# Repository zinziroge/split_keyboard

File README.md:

# split_keyboard
split_keyboard.

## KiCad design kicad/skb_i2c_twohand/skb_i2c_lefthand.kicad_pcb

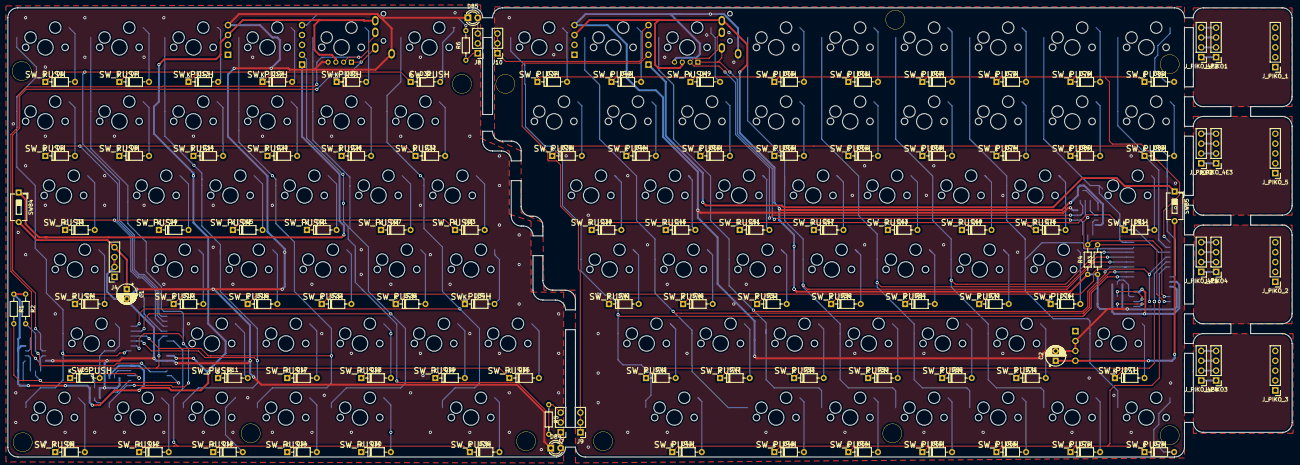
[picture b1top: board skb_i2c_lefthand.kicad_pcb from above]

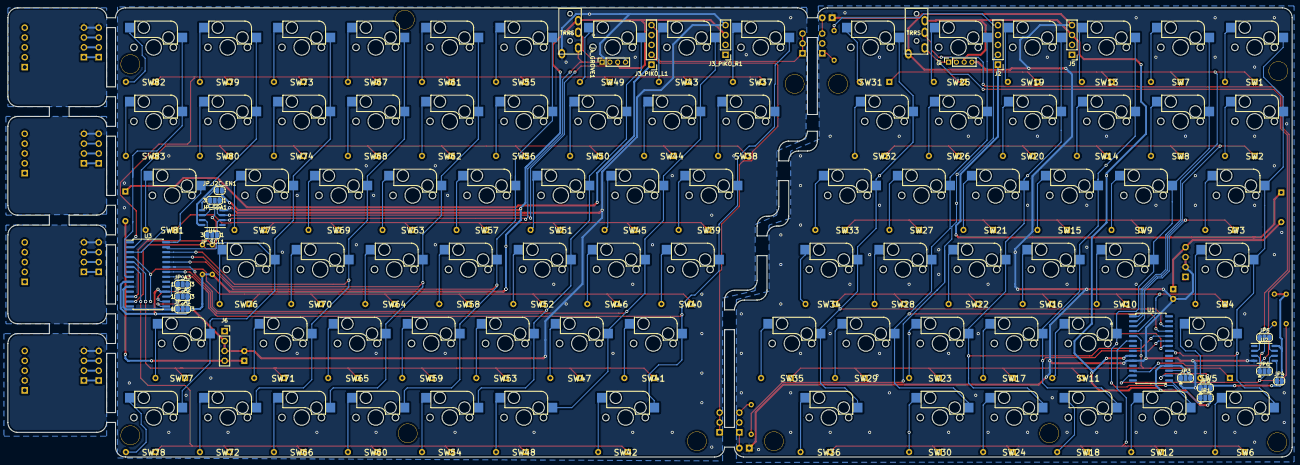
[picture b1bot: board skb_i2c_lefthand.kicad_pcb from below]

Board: 2 copper layers, 330.5 x 115.6 mm, 231 parts (108 on the bottom side), 162 nets.

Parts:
C1, C2: CP; CP_Radial_D5.0mm_P2.50mm
D1, D2, D3, D4, D5, D6, D7, D8, D9, D10, D11, D12, D13, D14, D15, D16, D17, D18, D19, D20, D21, D22, D23, D24, D25, D26, D27, D28, D29, D30, D31, D32, D33, D34, D35, D36, D37, D38, D39, D40, D41, D42, D43, D44, D45, D46, D47, D48, D49, D50, D51, D52, D53, D54, D55, D56, D57, D58, D59, D60, D61, D62, D63, D64, D65, D66, D67, D68, D69, D70, D71, D72, D73, D74, D75, D76, D77, D78, D79, D80, D81, D82, D83: 1N4148; D_DO-35_SOD27_P7.62mm_Horizontal
D84, D85: LED; LED_D3.0mm
J1, J2_TRRS1: MJ-4PP-9; MJ-4PP-9_1side
J2, J3_PIKO_L1: Conn_01x05_Male; PinHeader_1x05_P2.54mm_Vertical
J3, J4_GROVE1: Conn_01x04_Male; PinSocket_1x04_P2.00mm_Vertical
J3_PIKO_R1, J5: Conn_01x04_Male; PinHeader_1x04_P2.54mm_Vertical
J4: Power; PinSocket_1x04_P2.54mm_Vertical
J6: Conn_01x04; PinSocket_1x04_P2.54mm_Vertical
J7, J8, J9, J10: Conn_01x03; PinHeader_1x03_P2.54mm_Vertical
JP1: I2C_A0; SolderJumper-3_P1.3mm_Open_RoundedPad1.0x1.5mm
JP2: I2C_A1; SolderJumper-3_P1.3mm_Open_RoundedPad1.0x1.5mm
JP3: I2C_A2; SolderJumper-3_P1.3mm_Open_RoundedPad1.0x1.5mm
JP4: I2C_EN; SolderJumper-2_P1.3mm_Open_RoundedPad1.0x1.5mm
JP5: I2C_SCL; SolderJumper-3_P1.3mm_Open_RoundedPad1.0x1.5mm
JP6: I2C_SDA; SolderJumper-3_P1.3mm_Open_RoundedPad1.0x1.5mm
JP_A1: I2C_A0; SolderJumper-3_P1.3mm_Open_RoundedPad1.0x1.5mm_NumberLabels
JP_A2: I2C_A1; SolderJumper-3_P1.3mm_Open_RoundedPad1.0x1.5mm_NumberLabels
JP_A3: I2C_A2; SolderJumper-3_P1.3mm_Open_RoundedPad1.0x1.5mm_NumberLabels
JP_I2C_EN1: I2C_EN; SolderJumper-2_P1.3mm_Open_RoundedPad1.0x1.5mm
JP_SCL1: I2C_A2; SolderJumper-3_P1.3mm_Open_RoundedPad1.0x1.5mm_NumberLabels
JP_SDA1: I2C_A2; SolderJumper-3_P1.3mm_Open_RoundedPad1.0x1.5mm_NumberLabels
J_PIKO1, J_PIKO2, J_PIKO3, J_PIKO4: Conn_01x04_Male; PinHeader_1x04_P2.54mm_Vertical
J_PIKO_1, J_PIKO_2, J_PIKO_3, J_PIKO_5: Conn_01x05_Male; PinHeader_1x05_P2.54mm_Vertical
J_PIKO_4E1, J_PIKO_4E2, J_PIKO_4E3, J_PIKO_4E4: Conn_01x04_Male; PinHeader_1x04_P2.54mm_Vertical
R1, R2, R3, R4, R5, R6: R; R_Axial_DIN0204_L3.6mm_D1.6mm_P7.62mm_Horizontal
Ref**: Val**; HOLE
Ref**#2, Ref**#3, Ref**#4, Ref**#5, Ref**#6, Ref**#7, Ref**#8, Ref**#9, Ref**#10, Ref**#11: Val**; HOLE
SW1, SW2, SW3, SW4, SW5, SW6, SW7, SW8, SW9, SW10, SW11, SW12, SW13, SW14, SW15, SW16, SW17, SW18, SW19, SW20, SW21, SW22, SW23, SW24, SW25, SW26, SW27, SW28, SW29, SW30, SW31, SW32, SW33, SW34, SW35, SW36, SW37, SW38, SW39, SW40, SW41, SW42, SW43, SW44, SW45, SW46, SW47, SW48, SW49, SW50, SW51, SW52, SW53, SW54, SW55, SW56, SW57, SW58, SW59, SW60, SW61, SW62, SW63, SW64, SW65, SW66, SW67, SW68, SW69, SW70, SW71, SW72, SW73, SW74, SW75, SW76, SW77, SW78, SW79, SW80, SW81, SW82, SW83: SW_PUSH; Kailh_MX_Socket
SW84, SW85: SW_DIP_x01; SW_DIP_SPSTx01_Slide_6.7x4.1mm_W7.62mm_P2.54mm_LowProfile
U1, U3: MCP23017_SO; SOIC-28W_7.5x17.9mm_P1.27mm
U2, U4: PCA9515AD; SOP-8_3.9x4.9mm_P1.27mm

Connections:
COL_0: SW37.1, SW38.1, SW39.1, SW40.1, SW41.1, SW42.1, U3.21
COL_1: SW43.1, SW44.1, SW45.1, SW46.1, SW47.1, SW48.1, U3.22
COL_2: SW49.1, SW50.1, SW51.1, SW52.1, SW53.1, SW54.1, U3.23
COL_3: SW55.1, SW56.1, SW57.1, SW58.1, SW59.1, SW60.1, U3.24
COL_4: SW61.1, SW62.1, SW63.1, SW64.1, SW65.1, SW66.1, U3.25
COL_5: SW67.1, SW68.1, SW69.1, SW70.1, SW71.1, SW72.1, U3.26
COL_6: SW73.1, SW74.1, SW75.1, SW76.1, SW77.1, SW78.1, U3.27
COL_7: SW79.1, SW80.1, SW81.1, U3.28
COL_8: SW82.1, SW83.1, U3.8
G22: J3_PIKO_L1.2, J9.1, J9.2, J9.3
G33: J3_PIKO_L1.5, J10.1, J10.2, J10.3
GND: C2.2, J2_TRRS1.A, J3_PIKO_R1.4, J4_GROVE1.4, J6.2, J6.3, JP_A1.1, JP_A2.1, JP_A3.1, U3.10, U4.4
L_COL_0: SW1.1, SW2.1, SW3.1, SW4.1, SW5.1, SW6.1, U1.21
L_COL_1: SW7.1, SW8.1, SW9.1, SW10.1, SW11.1, SW12.1, U1.22
L_COL_2: SW13.1, SW14.1, SW15.1, SW16.1, SW17.1, SW18.1, U1.23
L_COL_3: SW19.1, SW20.1, SW21.1, SW22.1, SW23.1, SW24.1, U1.24
L_COL_4: SW25.1, SW26.1, SW27.1, SW28.1, SW29.1, SW30.1, U1.25
L_COL_5: SW31.1, SW32.1, SW33.1, SW34.1, SW35.1, SW36.1, U1.26
L_G22: J2.2, R5.2
L_G33: J2.5, R6.2
L_GND: C1.2, D84.1, D85.1, J1.A, J3.4, J4.2, J4.3, J5.4, JP1.1, JP2.1, JP3.1, U1.10, U2.4
L_ROW_0: D1.1, D7.1, D13.1, D19.1, D25.1, D31.1, U1.1
L_ROW_1: D2.1, D8.1, D14.1, D20.1, D26.1, D32.1, U1.2
L_ROW_2: D3.1, D9.1, D15.1, D21.1, D27.1, D33.1, U1.3
L_ROW_3: D4.1, D10.1, D16.1, D22.1, D28.1, D34.1, U1.4
L_ROW_4: D5.1, D11.1, D17.1, D23.1, D29.1, D35.1, U1.5
L_ROW_5: D6.1, D12.1, D18.1, D24.1, D30.1, D36.1, U1.6
L_SCL_GROVE: J1.D, J3.1, JP5.1, U2.2
L_SCL_MCP: JP5.2, R2.2, U1.12
L_SDA_GROVE: J1.C, J3.2, JP6.1, U2.3
L_SDA_MCP: JP6.2, R1.2, U1.13
L_VCC3P3V: J2.1, SW84.1
L_VCC3P3V_T: C1.1, J4.4, SW84.2
L_VCC5V: J1.B, J3.3, J5.3, JP1.3, JP2.3, JP3.3, JP4.2, R1.1, R2.1, U1.9, U1.18, U2.8
unnamed: D1.2, SW1.2
unnamed: D2.2, SW2.2
unnamed: D3.2, SW3.2
unnamed: D4.2, SW4.2
unnamed: D5.2, SW5.2
unnamed: D6.2, SW6.2
unnamed: D7.2, SW7.2
unnamed: D8.2, SW8.2
unnamed: D9.2, SW9.2
unnamed: D10.2, SW10.2
unnamed: D11.2, SW11.2
unnamed: D12.2, SW12.2
unnamed: D13.2, SW13.2
unnamed: D14.2, SW14.2
unnamed: D15.2, SW15.2
unnamed: D16.2, SW16.2
unnamed: D17.2, SW17.2
unnamed: D18.2, SW18.2
unnamed: D19.2, SW19.2
unnamed: D20.2, SW20.2
unnamed: D21.2, SW21.2
unnamed: D22.2, SW22.2
unnamed: D23.2, SW23.2
unnamed: D24.2, SW24.2
unnamed: D25.2, SW25.2
unnamed: D26.2, SW26.2
unnamed: D27.2, SW27.2
unnamed: D28.2, SW28.2
unnamed: D29.2, SW29.2
unnamed: D30.2, SW30.2
unnamed: D31.2, SW31.2
unnamed: D32.2, SW32.2
unnamed: D33.2, SW33.2
unnamed: D34.2, SW34.2
unnamed: D35.2, SW35.2
unnamed: D36.2, SW36.2
unnamed: D37.2, SW37.2
unnamed: D38.2, SW38.2
unnamed: D39.2, SW39.2
unnamed: D40.2, SW40.2
unnamed: D41.2, SW41.2
unnamed: D42.2, SW42.2
unnamed: D43.2, SW43.2
unnamed: D44.2, SW44.2
unnamed: D45.2, SW45.2
unnamed: D46.2, SW46.2
unnamed: D47.2, SW47.2
unnamed: D48.2, SW48.2
unnamed: D49.2, SW49.2
unnamed: D50.2, SW50.2
unnamed: D51.2, SW51.2
unnamed: D52.2, SW52.2
unnamed: D53.2, SW53.2
unnamed: D54.2, SW54.2
unnamed: D55.2, SW55.2
unnamed: D56.2, SW56.2
unnamed: D57.2, SW57.2
unnamed: D58.2, SW58.2
unnamed: D59.2, SW59.2
unnamed: D60.2, SW60.2
unnamed: D61.2, SW61.2
unnamed: D62.2, SW62.2
unnamed: D63.2, SW63.2
unnamed: D64.2, SW64.2
unnamed: D65.2, SW65.2
unnamed: D66.2, SW66.2
unnamed: D67.2, SW67.2
unnamed: D68.2, SW68.2
unnamed: D69.2, SW69.2
unnamed: D70.2, SW70.2
unnamed: D71.2, SW71.2
unnamed: D72.2, SW72.2
unnamed: D73.2, SW73.2
unnamed: D74.2, SW74.2
unnamed: D75.2, SW75.2
unnamed: D76.2, SW76.2
unnamed: D77.2, SW77.2
unnamed: D78.2, SW78.2
unnamed: D79.2, SW79.2
unnamed: D80.2, SW80.2
unnamed: D81.2, SW81.2
unnamed: D82.2, SW82.2
unnamed: D83.2, SW83.2
unnamed: D84.2, J7.1
unnamed: D85.2, J8.3
unnamed: J7.3, R5.1
unnamed: J8.1, R6.1
unnamed: JP1.2, U1.15
unnamed: JP2.2, U1.16
unnamed: JP3.2, U1.17
unnamed: JP4.1, U2.5
unnamed: JP5.3, U2.7
unnamed: JP6.3, U2.6
unnamed: JP_A1.2, U3.15
unnamed: JP_A2.2, U3.16
unnamed: JP_A3.2, U3.17
unnamed: JP_I2C_EN1.1, U4.5
unnamed: JP_SCL1.3, U4.7
unnamed: JP_SDA1.3, U4.6
unnamed: J_PIKO1.1, J_PIKO_4E2.1
unnamed: J_PIKO1.2, J_PIKO_4E2.2
unnamed: J_PIKO1.3, J_PIKO_4E2.3
unnamed: J_PIKO1.4, J_PIKO_4E2.4
unnamed: J_PIKO2.1, J_PIKO_4E3.1
unnamed: J_PIKO2.2, J_PIKO_4E3.2
unnamed: J_PIKO2.3, J_PIKO_4E3.3
unnamed: J_PIKO2.4, J_PIKO_4E3.4
unnamed: J_PIKO3.1, J_PIKO_4E4.1
unnamed: J_PIKO3.2, J_PIKO_4E4.2
unnamed: J_PIKO3.3, J_PIKO_4E4.3
unnamed: J_PIKO3.4, J_PIKO_4E4.4
unnamed: J_PIKO4.1, J_PIKO_4E1.1
unnamed: J_PIKO4.2, J_PIKO_4E1.2
unnamed: J_PIKO4.3, J_PIKO_4E1.3
unnamed: J_PIKO4.4, J_PIKO_4E1.4
ROW_0: D37.1, D43.1, D49.1, D55.1, D61.1, D67.1, D73.1, D79.1, D82.1, U3.1
ROW_1: D38.1, D44.1, D50.1, D56.1, D62.1, D68.1, D74.1, D80.1, D83.1, U3.2
ROW_2: D39.1, D45.1, D51.1, D57.1, D63.1, D69.1, D75.1, D81.1, U3.3
ROW_3: D40.1, D46.1, D52.1, D58.1, D64.1, D70.1, D76.1, U3.4
ROW_4: D41.1, D47.1, D53.1, D59.1, D65.1, D71.1, D77.1, U3.5
ROW_5: D42.1, D48.1, D54.1, D60.1, D66.1, D72.1, D78.1, U3.6
SCL_GROVE: J2_TRRS1.D, J4_GROVE1.1, JP_SCL1.1, U4.2
SCL_MCP: JP_SCL1.2, R4.2, U3.12
SDA_GROVE: J2_TRRS1.C, J4_GROVE1.2, JP_SDA1.1, U4.3
SDA_MCP: JP_SDA1.2, R3.2, U3.13
VCC3P3V: J3_PIKO_L1.1, SW85.1
VCC3P3V_T: C2.1, J6.4, SW85.2
VCC5V: J2_TRRS1.B, J3_PIKO_R1.3, J4_GROVE1.3, JP_A1.3, JP_A2.3, JP_A3.3, JP_I2C_EN1.2, R3.1, R4.1, U3.9, U3.18, U4.8

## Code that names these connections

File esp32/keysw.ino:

/*
  physical map
*/
#include "keysw.h"

// physical map
// esp32
int col_pins[] = {
    PIN_COL_0,
    PIN_COL_1,
    PIN_COL_2,
    PIN_COL_3,
    PIN_COL_4,
    PIN_COL_5,
    PIN_COL_6,
    PIN_COL_7,
    PIN_COL_8,
};
int row_pins[] = {
    PIN_ROW_0,
    PIN_ROW_1,
    PIN_ROW_2,
    PIN_ROW_3,
    PIN_ROW_4,
    PIN_ROW_5,
    PIN_ROW_6,
    PIN_ROW_7,
    PIN_ROW_8,
};

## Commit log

2020-11-08 inital commit. lefthand pcb is almost routed.
2020-11-08 add righthand data.
2020-11-08 move righthand data.
2020-11-09 complete lefthand pcb.
2020-11-22 complete to design pcb, and export gerber data.
2020-11-29 sucessfully build.
2020-11-29 modify
2020-11-29 rename .c to .ino. change keymap.
2020-12-02 add keymaps at setup() for debug.
2020-12-06 modify keycode
2020-12-11 add I2C testcode.
2020-12-19 add CAD of I2C type keyboard.
2020-12-19 route roughly
2020-12-27 route
2020-12-30 add gerber files.
2021-01-16 add BleKeyboardJP.(cpp|h) files
2021-01-31 implemente I2C mode
2021-01-31 modify row2col to col2tow.
2021-01-31 modify row2col to col2row
2021-02-01 add MCP23017_ADDR_R
2021-02-01 modifier key does not work.
2021-02-01 modify MATRIX_ROWS, MATRIX_COLS.
2021-03-05 chagen key input behavior
2021-03-27 add deep sleep mode
2021-04-17 change keymap
2021-11-28 add period
